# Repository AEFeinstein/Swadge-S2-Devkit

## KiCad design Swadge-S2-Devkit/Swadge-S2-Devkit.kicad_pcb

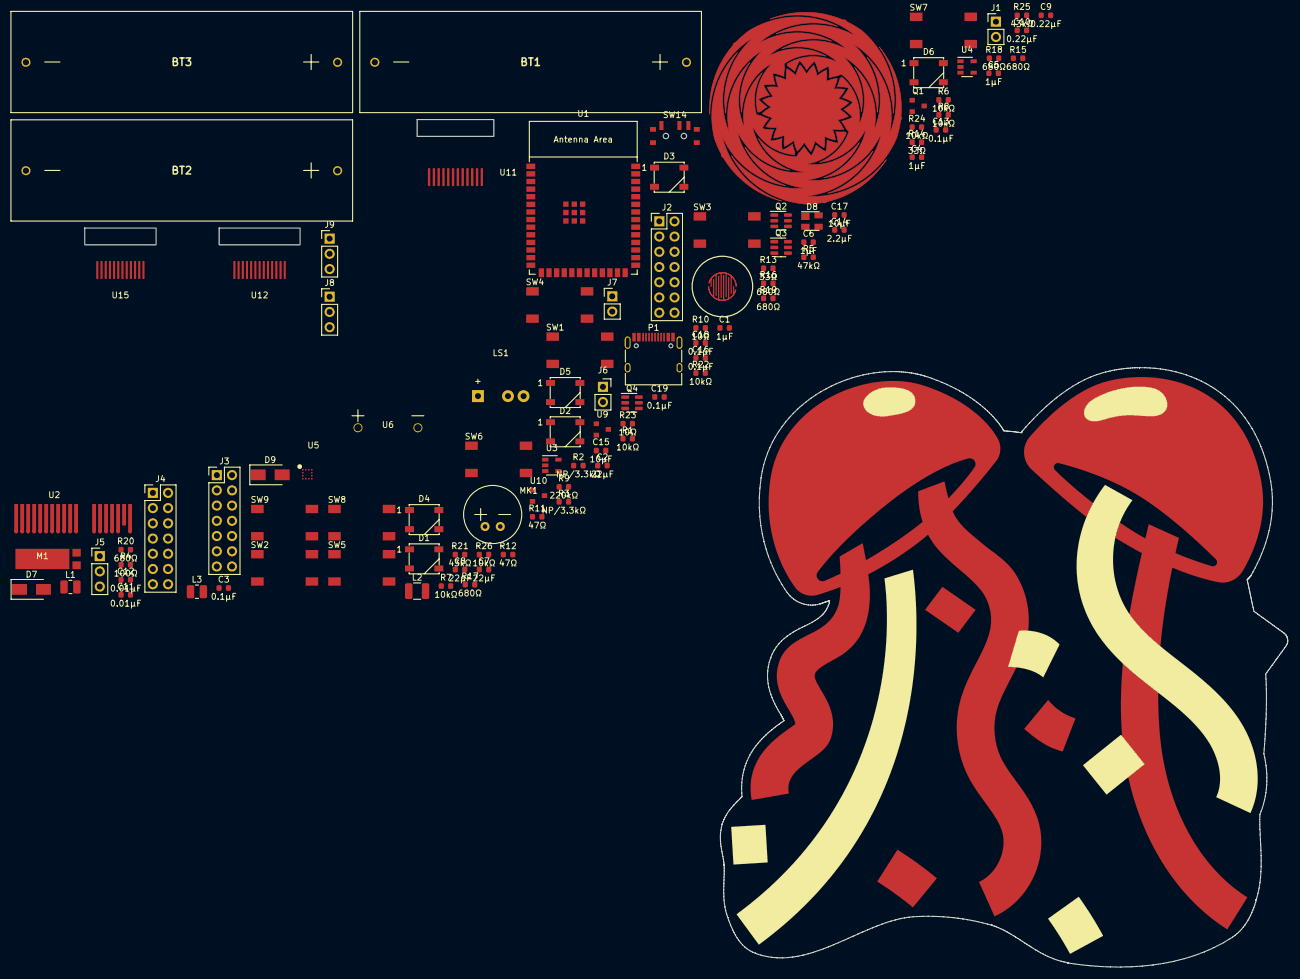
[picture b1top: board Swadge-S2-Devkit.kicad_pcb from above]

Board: 2 copper layers, 200.7 x 141.4 mm, 100 parts (0 on the bottom side), 83 nets, no tracks yet.

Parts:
BT1, BT2, BT3: Battery; 2460
C1, C4, C5, C6: 1μF; C_0603_1608Metric
C2, C7, C8: 22μF; C_0603_1608Metric
C3, C13, C16, C18, C19: 0.1μF; C_0603_1608Metric
C9, C10: 0.22μF; C_0603_1608Metric
C11, C12: 0.01μF; C_0603_1608Metric
C14: 2.2μF; C_0603_1608Metric
C15, C17: 10μF; C_0603_1608Metric
D1, D2, D3, D4, D5, D6: WS2812B; LED_WS2812B_PLCC4_5.0x5.0mm_P3.2mm
D7, D9: D; D_SMA
D8: SP0503BAHT; SOT-143
J1: CurrentMonitor; PinHeader_1x02_P2.54mm_Vertical
J2: DEBUG_BANK_C; PinHeader_2x07_P2.54mm_Vertical
J3: DEBUG_BANK_B; PinHeader_2x07_P2.54mm_Vertical
J4: DEBUG_BANK_A; PinHeader_2x07_P2.54mm_Vertical
J5: MICSEL; PinHeader_1x03_P2.54mm_Vertical
J6: TRYMIC; PinSocket_1x02_P2.54mm_Vertical
J7: LEDK_J; PinHeader_1x02_P2.54mm_Vertical
J8: LCD18; PinHeader_1x03_P2.54mm_Vertical
J9: LCD28; PinHeader_1x03_P2.54mm_Vertical
L1, L3: 2.2uH; L_1008_2520Metric
L2: 100uH; L_1210_3225Metric
LS1: Buzzer; Buzzer_12x9.5RM7.6
M1: VZ43FC1B5640007L
MK1: Microphone; CMA-4544PF-W
P1: USB_C_Plug_USB2.0; USB_C_Receptacle_HRO_TYPE-C-31-M-12
Q1: Q_N_FET; SOT-23
Q2, Q3, Q4: AP2003_PN_FET; SOT-23-6
R1, R6, R7, R8, R22, R24, R26: 10kΩ; R_0603_1608Metric
R2, R3: NP/3.3kΩ; R_0603_1608Metric
R4: 100Ω; R_0603_1608Metric
R5: 47kΩ; R_0603_1608Metric
R9: 220kΩ; R_0603_1608Metric
R10, R23: 10Ω; R_0603_1608Metric
R11, R12: 47Ω; R_0603_1608Metric
R13, R14: 33Ω; R_0603_1608Metric
R15, R16, R17, R18, R19, R20: 680Ω; R_0603_1608Metric
R21, R25: 43kΩ; R_0603_1608Metric
SW1, SW2, SW3, SW4, SW5, SW6, SW7, SW8, SW9: 4-1437565-2; SW_4-1437565-2
SW10: BLISTER_SILICONE_BUTTON; BTC007_Button_Silicone
SW11: touch-ring-6; Touch_Teeth_5
SW14: SW_SPDT; SW_SPDT_PCM12
U1: ESP32-S2-SOLO
U2: BUS_PCIexpress
U3: MT3410; SOT-23-5
U4: GS321-TR; SOT-23-5
U5: QMA7981; QMA6981
U6: INGHAi_GSPK2308P-8R0.5W; INGHAi GSPK2308P-8R0.5W
U9: GENERIC_LDO_1.8; SOT-23
U10: GENERIC_LDO_2.8; SOT-23
U11: LCD_240x240_1.3_12
U12: LCD_135x240_1.14_13
U15: LCD_240x240_1.54_12

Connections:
5VIN: D8.4 (K), D9.2 (A), P1.A4_B9 (VBUS), P1.A9_B4 (VBUS)
+3V3: C2.1, C3.1, C4.1, C5.1, C6.1, C12.1, C13.1, C14.1, C15.2, C16.1, C17.1, D1.1 (VDD), D2.1 (VDD), D3.1 (VDD), D4.1 (VDD), D5.1 (VDD), D6.1 (VDD), D7.1 (K), J4.2, J8.1, J9.1, L1.1, L3.1, M1.2 (+), Q4.2 (S2), R1.1, R2.2, R3.1, R10.2, R25.2, U1.2 (3V3), U2.A8, U2.B8, U5.3 (VDDIO), U5.7 (VDD), U5.10 (SENB), U9.3 (IN), U10.3 (IN), U12.10 (VDD), U15.4 (VDD)
+5V: D9.1 (K), J1.2, U2.A18, U2.B18
BATTMID: BT1.1 (+), BT2.2 (-)
BATTMID2: BT2.1 (+), BT3.2 (-)
BATTPLUS: BT3.1 (+), SW14.3 (C)
BLISTER1: J4.7, SW10.2, U1.7 (GPIO7/TOUCH7/ADC1_CH6)
BTN_1: J4.4, SW1.1, SW1.2, U1.4 (GPIO4/TOUCH4/ADC1_CH3)
BTN_2: J4.5, SW2.1, SW2.2, U1.5 (GPIO5/TOUCH5/ADC1_CH4)
BTN_3: J3.14, SW3.1, SW3.2, U1.26 (GPIO45), U2.A4, U2.B4
BTN_4: J3.4, SW4.1, SW4.2, U1.16 (GPIO46), U2.A3, U2.B3
BTN_5: J4.8, SW5.1, SW5.2, U1.8 (GPIO15/U0RTS/ADC2_CH4/XTAL_32K_P)
BTN_6: J2.2, SW6.1, SW6.2, U1.39 (GPIO1/TOUCH1/ADC1_CH0)
BTN_7: J2.3, SW7.1, SW7.2, U1.38 (GPIO2/TOUCH2/ADC1_CH1)
BTN_8: J2.14, SW8.1, SW8.2, U1.27 (GPIO0), U2.A2, U2.B2
BTN_9: J3.3, SW9.1, SW9.2, U1.15 (GPIO3/TOUCH3/ADC1_CH2)
BZR: J2.8, R23.1, U1.33 (MTDO/GPIO40/CLK_OUT2)
DIPRAIL: L1.2, Q2.2 (S2), Q3.2 (S2)
EN: C1.1, J4.3, R1.2, U1.3 (EN)
GND: BT1.2 (-), C1.2, C2.2, C3.2, C4.2, C5.2, C6.2, C7.2, C8.1, C9.1, C12.2, C13.2, C14.2, C15.1, C16.2, C17.2, C18.2, C19.2, D1.3 (VSS), D2.3 (VSS), D3.3 (VSS), D4.3 (VSS), D5.3 (VSS), D6.3 (VSS), D8.1 (A), J2.1, J3.1, J3.2, J4.1, J6.1, J7.1, LS1.2, M1.1 (GND), MK1.1 (-), P1.A1_B12 (GND), P1.A12_B1 (GND), P1.S1 (SHIELD), Q1.2 (S), Q2.5 (S1), Q3.5 (S1), Q4.5 (S1), R6.1, R22.2, R24.1, R26.2, SW1.3, SW1.4, SW2.3, SW2.4, SW3.3, SW3.4, SW4.3, SW4.4, SW5.3, SW5.4, SW6.3, SW6.4, SW7.3, SW7.4, SW8.3, SW8.4, SW9.3, SW9.4, SW10.1, SW14.4 (D), SW14.5 (E), SW14.6 (F), SW14.7 (G), U1.1 (GND), U1.40 (GND), U1.41 (GND), U2.A1, U2.B1, U3.2 (GND), U4.2 (VSS), U5.1 (AD0), U5.4 (RESV1), U5.8 (GNDIO), U5.9 (GND), U9.1 (GND), U10.1 (GND), U11.3 (GND), U11.10 (GND), U11.12 (GND), U12.8 (GND), U12.13 (GND), U15.1 (GND), U15.5 (GND), U15.6 (GND), U15.12 (GND)
LCD18: C18.1, J8.2, U11.5 (VDD18)
LCD28: C19.1, J9.2, U11.4 (VDD28)
LED: J2.9, R4.2, U1.32 (MTCK/GPIO39/CLK_OUT3), U2.A17, U2.B17
LED_OUT: D6.2 (DOUT), U2.A11, U2.B11
MIC: J4.12, J5.2, U1.12 (GPIO8/TOUCH8/ADC1_CH7)
MOTOR: J4.9, Q1.1 (G), U1.9 (GPIO16/U0CTS/ADC2_CH5/XTAL_32K_N)
unnamed: C7.1, R21.2, SW14.2 (B), U3.1 (EN), U3.4 (VIN)
unnamed: C8.2, C9.2, R5.2, R7.1, R10.1, U4.5 (VDD)
unnamed: C10.1, R8.2
unnamed: C10.2, J5.1, J6.2, MK1.2 (+), R7.2
unnamed: C11.1, J5.3, R9.1, U4.4 (OUT)
unnamed: C11.2, R8.1, R9.2, U4.3 (IN-)
unnamed: D1.2 (DOUT), D2.4 (DIN)
unnamed: D1.4 (DIN), R4.1
unnamed: D2.2 (DOUT), D3.4 (DIN)
unnamed: D3.2 (DOUT), D4.4 (DIN)
unnamed: D4.2 (DOUT), D5.4 (DIN)
unnamed: D5.2 (DOUT), D6.4 (DIN)
unnamed: D7.2 (A), M1.3 (-), Q1.3 (D)
unnamed: D8.2 (K), P1.A6 (DP1), R13.2
unnamed: D8.3 (K), P1.A7 (DN1), R14.2
unnamed: J1.1, SW14.1 (A)
unnamed: J8.3, U9.2 (OUT)
unnamed: J9.3, U10.2 (OUT)
unnamed: L2.1, Q4.4 (D2)
unnamed: L3.2, U3.3 (LX)
unnamed: LS1.1, R23.2
unnamed: Q2.4 (D2), Q2.6 (D1), U6.2 (-)
unnamed: Q3.4 (D2), Q3.6 (D1), U6.1 (+)
unnamed: R5.1, R6.2, U4.1 (IN+)
unnamed: R11.2, U5.2 (SDX)
unnamed: R12.2, U5.12 (SCX)
unnamed: R15.1, SW11.1 (0)
unnamed: R16.1, SW11.2 (60)
unnamed: R17.1, SW11.3 (120)
unnamed: R18.1, SW11.4 (180)
unnamed: R19.1, SW11.5 (240)
unnamed: R20.1, SW11.6 (300)
unnamed: R24.2, R25.1, U3.5 (FB)
RX: J2.5, U1.36 (U0RXD/GPIO44/CLK_OUT2), U2.A16, U2.B16
SCL: J4.11, R2.1, R12.1, U1.11 (GPIO18/U1RXD/ADC2_CH7/DAC_2/CLK_OUT3)
SDA: J4.10, R3.2, R11.1, U1.10 (GPIO17/U1TXD/ADC2_CH6/DAC_1)
SP+: J2.6, Q3.1 (G1), Q3.3 (G2), U1.35 (MTMS/GPIO42)
SP-: J2.7, Q2.1 (G1), Q2.3 (G2), U1.34 (MTDI/GPIO41/CLK_OUT1)
TFTATN: J3.12, Q4.1 (G1), U1.24 (SPIIO4/GPIO33/FSPIHD)
TFTATP: J2.13, Q4.3 (G2), U1.28 (SPIIO6/GPIO35/FSPID)
TFT_CS: J3.13, U1.25 (SPIIO5/GPIO34/FSPICS0), U11.6 (LCMCS), U12.7 (CS), U15.8 (CS)
TFT_LEDA: L2.2, Q4.6 (D1), U11.2 (LEDA), U12.12 (LEDA), U15.3 (LEDA)
TFT_LEDK: J7.2, U11.1 (LEDK), U12.11 (LEDK), U15.2 (LEDK)
TFT_RESET: J2.10, U1.31 (GPIO38/FSPIWP), U11.7 (LCM-RST), U12.6 (RESET), U15.11 (RESET)
TFT_RS: J3.11, R26.1, U1.23 (GPIO21), U11.11 (LCM-CD), U12.5 (RS), U15.7 (A0)
TFT_SCL: J2.12, U1.29 (SPIIO7/GPIO36/FSPICLK), U11.8 (LCM-SCL), U12.4 (SCL), U15.9 (SCLK)
TFT_SDA: J2.11, U1.30 (SPIDQS/GPIO37/FSPIQ), U11.9 (LCM-SDA), U12.3 (SDA), U15.10 (SDA)
TOUCH_1: R15.2, U1.17 (GPIO9/TOUCH9/ADC1_CH8/FSPIHD)
TOUCH_2: R16.2, U1.18 (GPIO10/TOUCH10/ADC1_CH9/FSPICS0/FSPIIO4)
TOUCH_3: R17.2, U1.19 (GPIO11/TOUCH11/ADC2_CH0/FSPID/FSPIIO5)
TOUCH_4: R18.2, U1.20 (GPIO12/TOUCH12/ADC2_CH1/FSPICLK/FSPIIO6)
TOUCH_5: R19.2, U1.21 (GPIO13/TOUCH13/ADC2_CH2/FSPIQ/FSPIIO7)
TOUCH_6: R20.2, U1.22 (GPIO14/TOUCH14/ADC2_CH3/FSPIWP/FSPIDQS)
TX: J2.4, U1.37 (U0TXD/GPIO43/CLK_OUT1), U2.A15, U2.B15
USB_D+: J4.14, R13.1, U1.14 (GPIO20/U1CTS/ADC2_CH9/CLK_OUT1/USB_D+)
USB_D-: J4.13, R14.1, U1.13 (GPIO19/U1RTS/ADC2_CH8/CLK_OUT2/USB_D-)
VMON: J4.6, R21.1, R22.1, U1.6 (GPIO6/TOUCH6/ADC1_CH5)

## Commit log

2022-03-26 Switched to controller PCB
2022-04-05 Ripped all traces, adjusted part placement
2022-04-05 Added annotated schematic
2022-06-26 Messing around with another party ball
